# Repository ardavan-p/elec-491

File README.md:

# ECE Capstone Project TL81 - Wirelessly Powered Tire Pressure Monitoring System

## Introduction
The following repository contains all design components for UBC ECE capstone project TL81 - Wirelessly Powered Tire Pressure Monitoring System

## Design Components
The following directories contain primary design components. 

### Graphical User Interface for TPMS
The source code for the GUI which was designed for demonstration purposes is located in the `gui/` folder. It is design in the Python.

### ECU Source Code
The firmware for the master ECU used in the demonstration is located in the `ecu/` folder. It is all written in C, for the STM32F103RCT6 microcontroller.

### Power Transmitter Node
All design files for the power transmitter node is located in the `ptn/` and `enclosure/ptn/` directories. <br>

The PCB design files for the power transmitter node are located in `ptn/pcb/`. The PCB is designed using the KiCad PCB design software. <br>

The firmware source code for the power transmitter node is located in `ptn/fw/`. It is all written in C, for the STM32F103C8T6 microcontroller. <br>

The physical enclosure for the power transmitter node is located in `enclosure/ptn/`. The PTN enclosure was designed using SolidWorks.

### Sensor Node
All design files for the sensor node is located in the `sn/` directory. <br>

The PCB design files for the sensor node are located in `sn/rev-2/pcb/sensor-node-v2/`. The PCB is designed using the KiCad PCB design software. <br>

The firmware source code for the final revision of the sensor node is located in `sn/rev-2/fw/sensor-node-v2/`. It is all written in C, for the STM32U031K8U6 microcontroller. <br>

## Capstone Video
All assets for the video created for this project is located in the `video/` folder.

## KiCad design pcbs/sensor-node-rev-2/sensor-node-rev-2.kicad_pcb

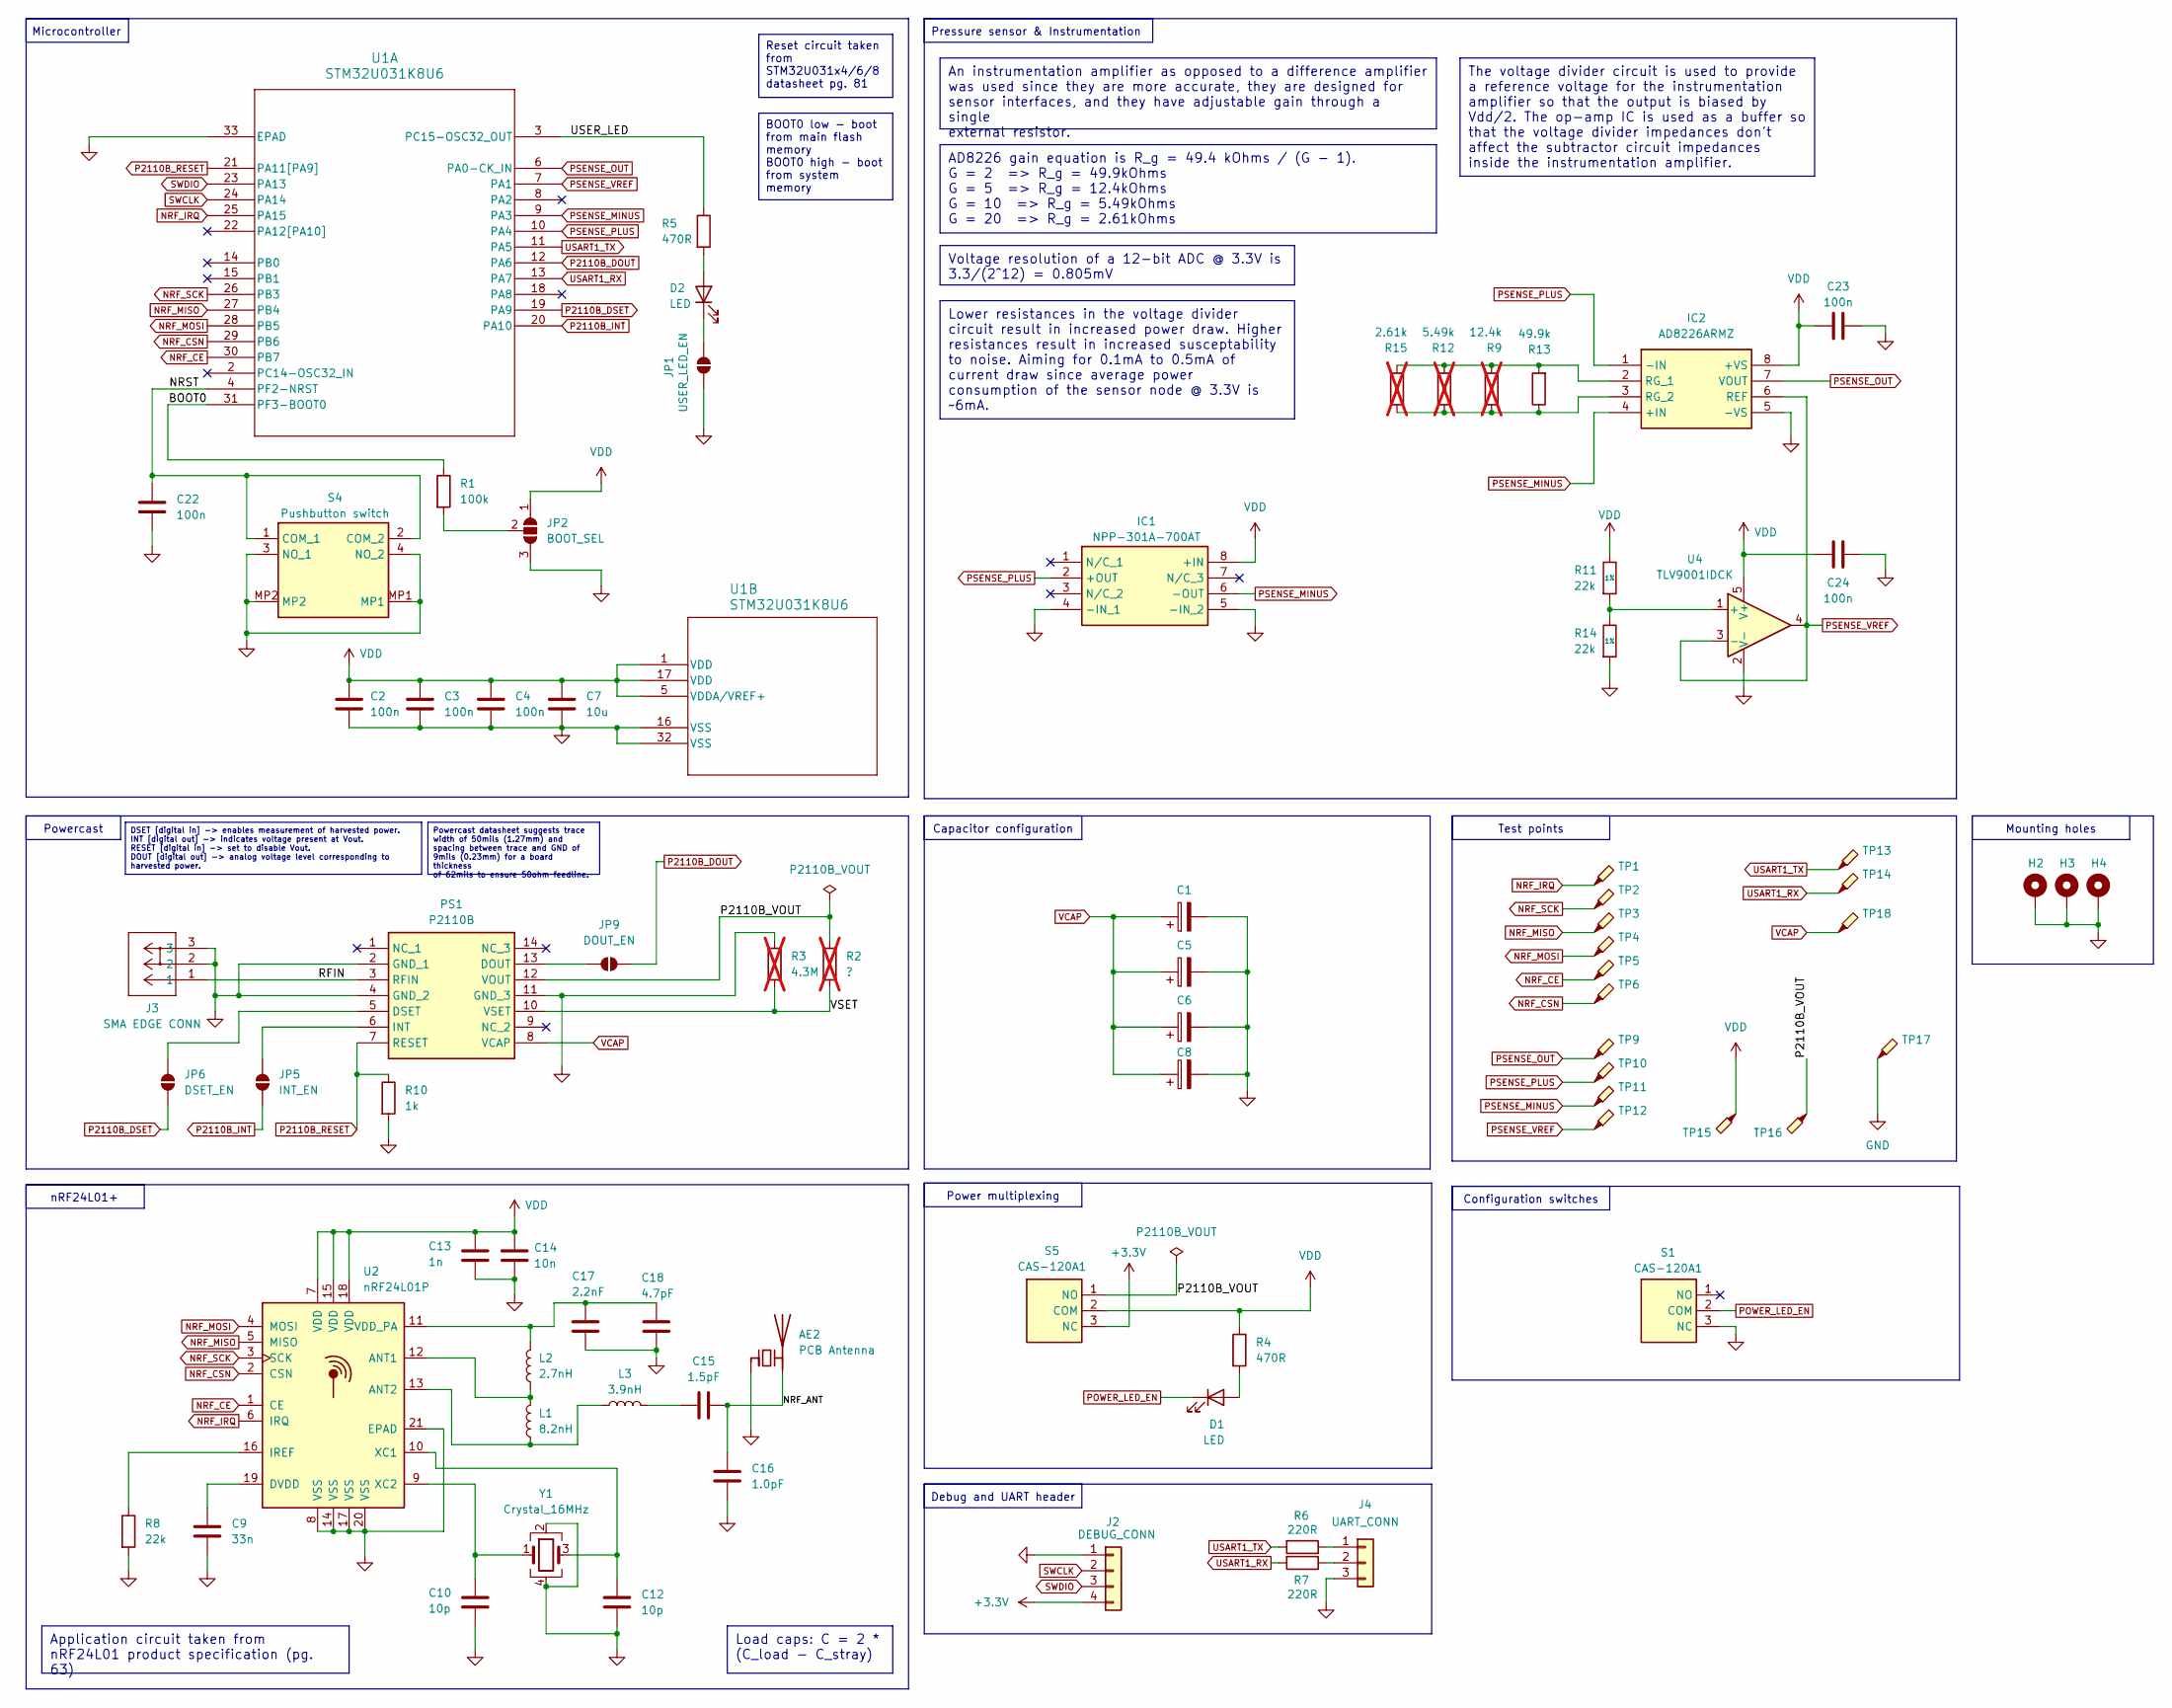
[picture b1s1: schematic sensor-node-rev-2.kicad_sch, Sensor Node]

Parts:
AE2: PCB Antenna; TI_2G4_Inv_F_Antenna_1
C1, C5, C6, C8: C_Polarized; CAPPM7362X375N; Manufacturer_Part_Number T520D108M2R5ATE030; Mouser Part Number 80-T520D108M2R5ATE30
C2, C3, C4, C22, C23, C24: 100n; C_0402_1005Metric; Manufacturer_Part_Number GRM155R61E104KA87J; Mouser Part Number 81-GRM155R61E104KA7J
C7: 10u; C_0402_1005Metric; Manufacturer_Part_Number GRM155R60J106ME05D; Mouser Part Number 81-GRM155R60J106M05D
C9: 33n; C_0402_1005Metric; Manufacturer_Part_Number GRM155R71H333KE14J; Mouser Part Number 81-GRM155R71H333KE4J
C10, C12: 10p; C_0402_1005Metric; Manufacturer_Part_Number GRM1555C1E120GA01D; Mouser Part Number 81-GCM1555G1H120GA6J
C13: 1n; C_0402_1005Metric; Manufacturer_Part_Number GRM1555C1H102GA01D; Mouser Part Number 81-GRM1555C1H102GA1D
C14: 10n; C_0402_1005Metric; Manufacturer_Part_Number GRM155R71H103JA88D; Mouser Part Number 81-GRM155R71H103JA8D
C15: 1.5pF; C_0402_1005Metric; Manufacturer_Part_Number VJ0402A1R5BXQPW1BC; Mouser Part Number 77-VJ0402A1R5BXQPBC
C16: 1.0pF; C_0402_1005Metric; Manufacturer_Part_Number VJ0402A1R0BXQPW1BC; Mouser Part Number 77-VJ0402A1R0BXQPBC
C17: 2.2nF; C_0402_1005Metric; Manufacturer_Part_Number GRM155R71H222JA01D; Mouser Part Number 81-GRM36X222J50
C18: 4.7pF; C_0402_1005Metric; Manufacturer_Part_Number GCM1555C1H4R7BA16J; Mouser Part Number 81-GCM1555C1H4R7BA6J
D1, D2: LED; LED_0402_1005Metric; Manufacturer_Part_Number 150040GS73220; Mouser Part Number 710-150040GS73220
H2, H3, H4: MountingHole; MountingHole_2.2mm_M2_Pad
IC1: NPP-301A-700AT; SOIC127P610X280-8N; Mouser Part Number 527-NPP-301A-700AT
IC2: AD8226ARMZ; SOP65P490X110-8N; Mouser Part Number 584-AD8226ARMZ
J2: DEBUG_CONN; PinHeader_1x04_P2.54mm_Vertical
J3: SMA EDGE CONN; CONN_73251-1150_MOL; Manufacturer_Part_Number EMPCB.SMAFSTJ.B.HT; Mouser Part Number 960-EMPCB.SMAFSTJBHT
J4: UART_CONN; PinHeader_1x03_P2.54mm_Vertical
JP1: USER_LED_EN; SolderJumper-2_P1.3mm_Open_RoundedPad1.0x1.5mm
JP2: BOOT_SEL; SolderJumper-3_P1.3mm_Open_RoundedPad1.0x1.5mm
JP5: INT_EN; SolderJumper-2_P1.3mm_Open_RoundedPad1.0x1.5mm
JP6: DSET_EN; SolderJumper-2_P1.3mm_Open_RoundedPad1.0x1.5mm
JP9: DOUT_EN; SolderJumper-2_P1.3mm_Open_RoundedPad1.0x1.5mm
L1: 8.2nH; L_0402_1005Metric; Manufacturer_Part_Number LQG15HS8N2H02D; Mouser Part Number 81-LQG15HS8N2H02D
L2: 2.7nH; L_0402_1005Metric; Manufacturer_Part_Number LQG15HN2N7C02D; Mouser Part Number 81-LQG15HN2N7C02D
L3: 3.9nH; L_0402_1005Metric; Manufacturer_Part_Number LQG15HZ3N9C02D; Mouser Part Number 81-LQG15HZ3N9C02D
PS1: P2110B; Mouser Part Number 582-P2110B
R1: 100k; R_0402_1005Metric; Manufacturer_Part_Number ERJ-U02J104X; Mouser Part Number 667-ERJ-U02J104X
R2: ?; R_0402_1005Metric; not fitted
R3: 4.3M; R_0402_1005Metric; Manufacturer_Part_Number CRCW04024M32FKED; Mouser Part Number 71-CRCW04024M32FKED; not fitted
R4, R5: 470R; R_0402_1005Metric; Manufacturer_Part_Number ERJ-2RHD471X; Mouser Part Number 667-ERJ-2RHD471X
R6, R7: 220R; R_0402_1005Metric; Manufacturer_Part_Number ERJ-2RHD2200X; Mouser Part Number 667-ERJ-2RHD2200X
R8: 22k; R_0402_1005Metric; Manufacturer_Part_Number ERJ-H2RD2202X; Mouser Part Number 667-ERJ-H2RD2202X
R9: 12.4k; R_0402_1005Metric; Manufacturer_Part_Number ERJ-U02F1242X; Mouser Part Number 667-ERJ-U02F1242X; not fitted
R10: 1k; R_0402_1005Metric; Manufacturer_Part_Number ERJ-2GEJ102X; Mouser Part Number 667-ERJ-2GEJ102X
R11, R14: 22k; R_0402_1005Metric; Tolerance 1%; Manufacturer_Part_Number ERJ-H2RD2202X; Mouser Part Number 667-ERJ-H2RD2202X
R12: 5.49k; R_0402_1005Metric; Manufacturer_Part_Number ERJ-2RKF5491X; Mouser Part Number 667-ERJ-2RKF5491X; not fitted
R13: 49.9k; R_0402_1005Metric; Manufacturer_Part_Number ERJ-2RKF4992X; Mouser Part Number 667-ERJ-2RKF4992X
R15: 2.61k; R_0402_1005Metric; Manufacturer_Part_Number ERJ-U02F2611X; Mouser Part Number 667-ERJ-U02F2611X; not fitted
S1, S5: CAS-120A1; CAS120A1; Mouser Part Number 229-CAS-120A1
S4: Pushbutton switch; TS2134035BK160SMTTR; Mouser Part Number 179-134035BK160SMTTR
TP1, TP2, TP3, TP4, TP5, TP6, TP9, TP10, TP11, TP12: TestPoint_Pad_1.5x1.5mm; Manufacturer_Part_Number RCT-0C; Mouser Part Number 279-RCT-0C
TP13, TP14, TP15, TP16, TP17, TP18: TestPoint_Pad_2.0x2.0mm; Manufacturer_Part_Number RCT-0C; Mouser Part Number 279-RCT-0C
U1: STM32U031K8U6; QFN50P500X500X60-33N-D; Manufacturer_Part_Number STM32U031K8U6; Mouser Part Number 511-STM32U031K8U6
U2: nRF24L01P; QFN-20-1EP_4x4mm_P0.5mm_EP2.5x2.5mm; Manufacturer_Part_Number NRF24L01P; Mouser Part Number 949-NRF24L01P
U4: TLV9001IDCK; SOT-353_SC-70-5; Manufacturer_Part_Number TLV9001IDCKR; Mouser Part Number 595-TLV9001IDCKR
Y1: Crystal_16MHz; 830064296; Manufacturer_Part_Number 830064296; Mouser Part Number 710-830064296

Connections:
+3.3V: J2.4, S5.3 (NC)
/BOOT0: R1.1, U1.31 (PF3-BOOT0)
/NRF_ANT: AE2.2 (PCB_Trace), C15.2, C16.1
/NRST: C22.1, S4.1 (COM_1), S4.2 (COM_2), U1.4 (PF2-NRST)
/P2110B_VOUT: PS1.12 (VOUT), R2.1, S5.1 (NO), TP16.1
/RFIN: J3.1, PS1.3 (RFIN)
/USER_LED: R5.1, U1.3 (PC15-OSC32_OUT)
/VSET: PS1.10 (VSET), R2.2, R3.2
GND: AE2.1 (FEED), C1.2, C2.2, C3.2, C4.2, C5.2, C6.2, C7.2, C8.2, C9.2, C10.2, C12.2, C13.2, C14.2, C16.2, C17.1, C18.2, C22.2, C23.2, C24.2, H2.1, H3.1, H4.1, IC1.4 (-IN_1), IC1.5 (-IN_2), IC2.5 (-VS), J2.1, J3.2, J3.3, J4.3, JP1.1 (A), JP2.3 (B), PS1.2 (GND_1), PS1.4 (GND_2), PS1.11 (GND_3), R3.1, R8.2, R10.2, R14.2, S1.3 (NC), S4.3 (NO_1), S4.4 (NO_2), S4.MP1, S4.MP2, TP17.1, U1.16 (VSS), U1.32 (VSS), U1.33 (EPAD), U2.8 (VSS), U2.14 (VSS), U2.17 (VSS), U2.20 (VSS), U2.21 (EPAD), U4.2 (V-), Y1.2, Y1.4
NRF_CE: TP5.1, U1.30 (PB7), U2.1 (CE)
NRF_CSN: TP6.1, U1.29 (PB6), U2.2 (CSN)
NRF_IRQ: TP1.1, U1.25 (PA15), U2.6 (IRQ)
NRF_MISO: TP3.1, U1.27 (PB4), U2.5 (MISO)
NRF_MOSI: TP4.1, U1.28 (PB5), U2.4 (MOSI)
NRF_SCK: TP2.1, U1.26 (PB3), U2.3 (SCK)
unnamed: C15.1, L3.2
unnamed: D1.2 (A), R4.2
unnamed: D2.2 (A), R5.2
unnamed: D2.1 (K), JP1.2 (B)
unnamed: IC2.2 (RG_1), R9.2, R12.2, R13.2, R15.2
unnamed: IC2.3 (RG_2), R9.1, R12.1, R13.1, R15.1
unnamed: J4.1, R6.1
unnamed: J4.2, R7.1
unnamed: JP2.2 (C), R1.2
unnamed: JP5.2 (B), PS1.6 (INT)
unnamed: JP6.2 (B), PS1.5 (DSET)
unnamed: JP9.2 (B), PS1.13 (DOUT)
unnamed: L1.2, L2.1, U2.12 (ANT1)
unnamed: L1.1, L3.1, U2.13 (ANT2)
unnamed: C9.1, U2.19 (DVDD)
unnamed: R8.1, U2.16 (IREF)
unnamed: C17.2, C18.1, L2.2, U2.11 (VDD_PA)
unnamed: C12.1, U2.10 (XC1), Y1.3
unnamed: C10.1, U2.9 (XC2), Y1.1
unnamed: R11.2, R14.1, U4.1 (+)
P2110B_DOUT: JP9.1 (A), U1.12 (PA6)
P2110B_DSET: JP6.1 (A), U1.19 (PA9)
P2110B_INT: JP5.1 (A), U1.20 (PA10)
P2110B_RESET: PS1.7 (RESET), R10.1, U1.21 (PA11[PA9])
POWER_LED_EN: D1.1 (K), S1.2 (COM)
PSENSE_MINUS: IC1.6 (-OUT), IC2.4 (+IN), TP11.1, U1.9 (PA3)
PSENSE_OUT: IC2.7 (VOUT), TP9.1, U1.6 (PA0-CK_IN)
PSENSE_PLUS: IC1.2 (+OUT), IC2.1 (-IN), TP10.1, U1.10 (PA4)
PSENSE_VREF: IC2.6 (REF), TP12.1, U1.7 (PA1), U4.3 (-), U4.4
SWCLK: J2.2, U1.24 (PA14)
SWDIO: J2.3, U1.23 (PA13)
USART1_RX: R7.2, TP14.1, U1.13 (PA7)
USART1_TX: R6.2, TP13.1, U1.11 (PA5)
VCAP: C1.1, C5.1, C6.1, C8.1, PS1.8 (VCAP), TP18.1
VDD: C2.1, C3.1, C4.1, C7.1, C13.1, C14.1, C23.1, C24.1, IC1.8 (+IN), IC2.8 (+VS), JP2.1 (A), R4.1, R11.1, S5.2 (COM), TP15.1, U1.1 (VDD), U1.5 (VDDA/VREF+), U1.17 (VDD), U2.7 (VDD), U2.15 (VDD), U2.18 (VDD), U4.5 (V+)

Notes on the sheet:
Reset circuit taken from STM32U031x4/6/8 datasheet pg. 81
Lower resistances in the voltage divider circuit result in increased power draw. Higher resistances result in increased susceptability to noise. Aiming for 0.1mA to 0.5mA of current draw since average power consumption of the sensor node @ 3.3V is ~6mA.
AD8226 gain equation is R_g = 49.4 kOhms / (G - 1). G = 2 => R_g = 49.9kOhms G = 5 => R_g = 12.4kOhms G = 10 => R_g = 5.49kOhms G = 20 => R_g = 2.61kOhms
Voltage resolution of a 12-bit ADC @ 3.3V is 3.3/(2^12) = 0.805mV
Powercast datasheet suggests trace width of 50mils (1.27mm) and spacing between trace and GND of 9mils (0.23mm) for a board thickness of 62mils to ensure 50ohm feedline.
The voltage divider circuit is used to provide a reference voltage for the instrumentation amplifier so that the output is biased by Vdd/2. The op-amp IC is used as a buffer so that the voltage divider impedances don't affect the subtractor circuit impedances inside the instrumentation amplifier.
An instrumentation amplifier as opposed to a difference amplifier was used since they are more accurate, they are designed for sensor interfaces, and they have adjustable gain through a single external resistor.
BOOT0 low - boot from main flash memory BOOT0 high - boot from system memory
DSET [digital in] -> enables measurement of harvested power. INT [digital out] -> indicates voltage present at Vout. RESET [digital in] -> set to disable Vout. DOUT [digital out] -> analog voltage level corresponding to harvested power.
Application circuit taken from nRF24L01 product specification (pg. 63)
Load caps: C = 2 * (C_load - C_stray)
Test points
Capacitor configuration
nRF24L01+
Microcontroller
Powercast
Power multiplexing
Configuration switches
Debug and UART header
Mounting holes
Pressure sensor & Instrumentation

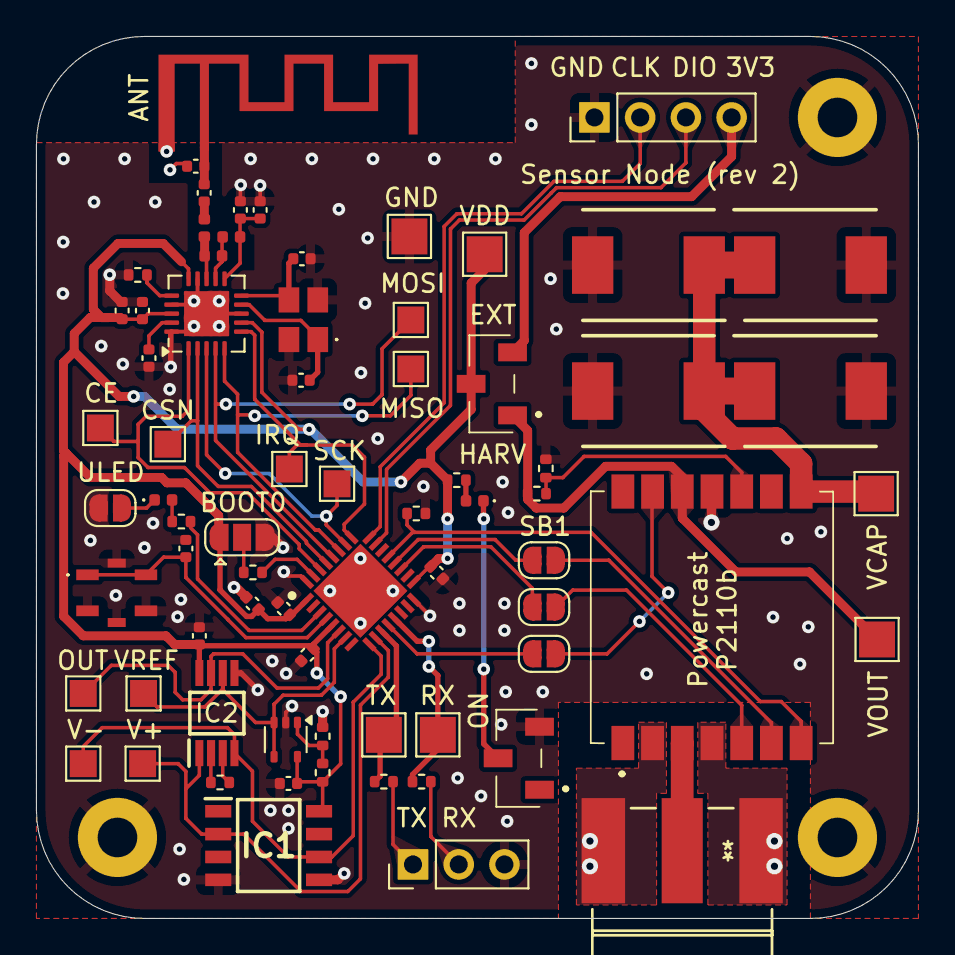
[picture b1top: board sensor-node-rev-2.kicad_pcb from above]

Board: 2 copper layers, 49.0 x 49.0 mm, 75 parts (0 on the bottom side), 50 nets.
